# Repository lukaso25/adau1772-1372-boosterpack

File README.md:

# adau1772-1372-boosterpack
4x2 Audio DSP boosterpack primary for EK-TM4C123GXL LaunchPad based on ADAU1772 or ADAU1372 codec.

PCB designed in Eagle 6

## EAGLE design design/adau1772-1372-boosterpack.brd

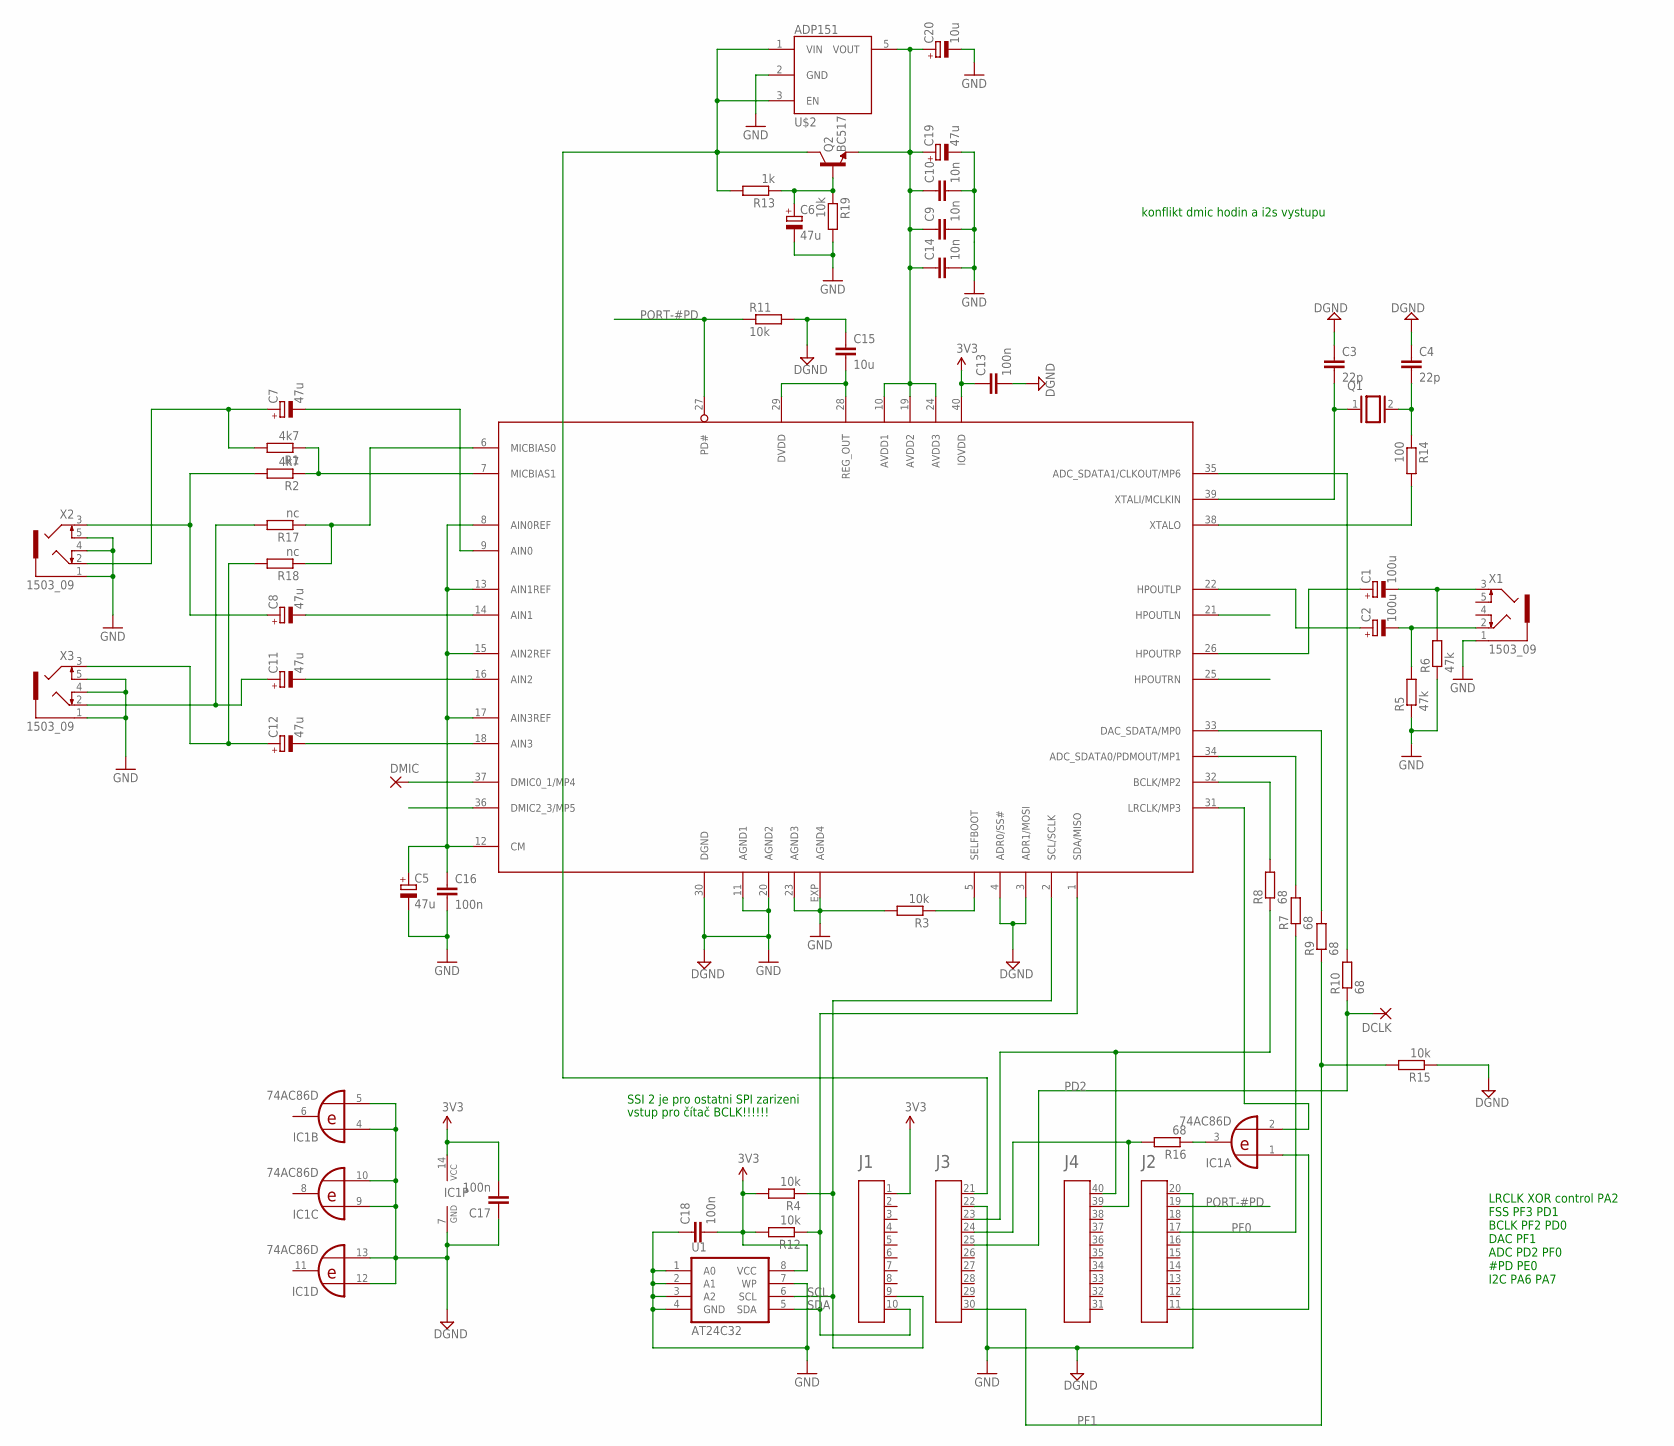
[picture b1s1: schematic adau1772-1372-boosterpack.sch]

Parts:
A1: HEADER4X10-BOOSTERPACK; 4X10-BOOSTERPACK
C1, C2: 100u; E2,5-7
C3, C4: 22p; C0805K
C5: 47u; SMC_C
C6, C7, C8, C11, C12, C19: 47u; E2-5
C9, C10, C14: 10n; C0805
C13, C16, C17, C18: 100n; C0805
C15: 10u; C0805
C20: 10u; SMC_A
DCLK: SMD2; SMD1,27-2,54
DMIC: SMD2; SMD1,27-2,54
IC1: 74AC86D; SO14
Q1: XTAL/S; QS
Q2: BC517; TO92-
R1, R2: 4k7; R1206
R3, R15: 10k; R1206
R4, R11, R12, R19: 10k; R0805
R5, R6: 47k; R0805
R7, R8, R9, R10, R16: 68; R1206
R13: 1k; R0805
R14: 100; R0805
R17, R18: nc; R1206
U1: AT24C32; SO08-8S1
U$1: ADAU1772; LFPSC-40
U$2: ADP151; SOT23-5
X1, X2, X3: 1503_09

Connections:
3.3V: A1.1, C13.1, C17.2, C18.2, IC1.14 (VCC), R4.2, R12.2, U1.8 (VCC), U$1.40 (IOVDD)
GND: A1.20, A1.22, C3.1, C4.1, C5.-, C6.-, C9.2, C10.2, C13.2, C14.2, C15.1, C16.2, C17.1, C18.1, C19.-, C20.-, IC1.4 (I0), IC1.5 (I1), IC1.7 (GND), IC1.9 (I0), IC1.10 (I1), IC1.12 (I0), IC1.13 (I1), R3.2, R5.1, R6.1, R11.2, R15.1, R19.2, U1.1 (A0), U1.2 (A1), U1.3 (A2), U1.4 (GND), U1.7 (WP), U$1.3 (ADR1/MOSI), U$1.4 (ADR0/SS#), U$1.11 (AGND1), U$1.20 (AGND2), U$1.23 (AGND3), U$1.30 (DGND), U$1.EXP (AGND4), U$2.2 (GND), X1.1, X2.1, X2.4, X2.5, X3.1, X3.4, X3.5
unnamed: C8.+, R2.2, X2.3
unnamed: C7.+, R1.2, X2.2
unnamed: C12.-, U$1.18 (AIN3)
unnamed: A1.21, Q2.3 (C), R13.2, U$2.1 (VIN), U$2.3 (EN)
unnamed: C12.+, R18.2, X3.3
unnamed: C11.+, R17.2, X3.2
unnamed: IC1.2 (I1), U$1.31 (LRCLK/MP3)
unnamed: C9.1, C10.1, C14.1, C19.+, C20.+, Q2.1 (E), U$1.10 (AVDD1), U$1.19 (AVDD2), U$1.24 (AVDD3), U$2.5 (VOUT)
unnamed: C1.+, U$1.26 (HPOUTRP)
unnamed: R1.1, R2.1, U$1.7 (MICBIAS1)
unnamed: C2.-, R5.2, X1.2
unnamed: C1.-, R6.2, X1.3
unnamed: R8.2, U$1.32 (BCLK/MP2)
unnamed: C2.+, U$1.22 (HPOUTLP)
unnamed: R7.2, U$1.34 (ADC_SDATA0/PDMOUT/MP1)
unnamed: R10.2, U$1.35 (ADC_SDATA1/CLKOUT/MP6)
unnamed: C3.2, Q1.1, U$1.39 (XTALI/MCLKIN)
unnamed: C4.2, Q1.2, R14.1
unnamed: R14.2, U$1.38 (XTALO)
unnamed: R9.2, U$1.33 (DAC_SDATA/MP0)
unnamed: DMIC.1, U$1.37 (DMIC0_1/MP4)
unnamed: C15.2, U$1.28 (REG_OUT), U$1.29 (DVDD)
unnamed: C11.-, U$1.16 (AIN2)
unnamed: R17.1, R18.1, U$1.6 (MICBIAS0)
unnamed: IC1.3 (O), R16.1
unnamed: A1.11, IC1.1 (I0)
unnamed: A1.24, A1.39, R16.2
unnamed: C6.+, Q2.2 (B), R13.1, R19.1
unnamed: A1.23, A1.40, R8.1
unnamed: R3.1, U$1.5 (SELFBOOT)
unnamed: C7.-, U$1.9 (AIN0)
unnamed: C8.-, U$1.14 (AIN1)
PD2: A1.25, DCLK.1, R10.1
PF0: A1.17, R7.1
PF1: A1.30, R9.1, R15.2
PORT-#PD: A1.19, R11.1, U$1.27 (PD#)
SCL: A1.9, R4.1, U1.6 (SCL), U$1.2 (SCL/SCLK)
SDA: A1.10, R12.1, U1.5 (SDA), U$1.1 (SDA/MISO)
VREF: C5.+, C16.1, U$1.8 (AIN0REF), U$1.12 (CM), U$1.13 (AIN1REF), U$1.15 (AIN2REF), U$1.17 (AIN3REF)

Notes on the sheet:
konflikt dmic hodin a i2s vystupu
SSI 2 je pro ostatni SPI zarizeni
vstup pro čítač BCLK!!!!!!
LRCLK XOR control PA2 FSS PF3 PD1 BCLK PF2 PD0 DAC PF1 ADC PD2 PF0 #PD PE0 I2C PA6 PA7

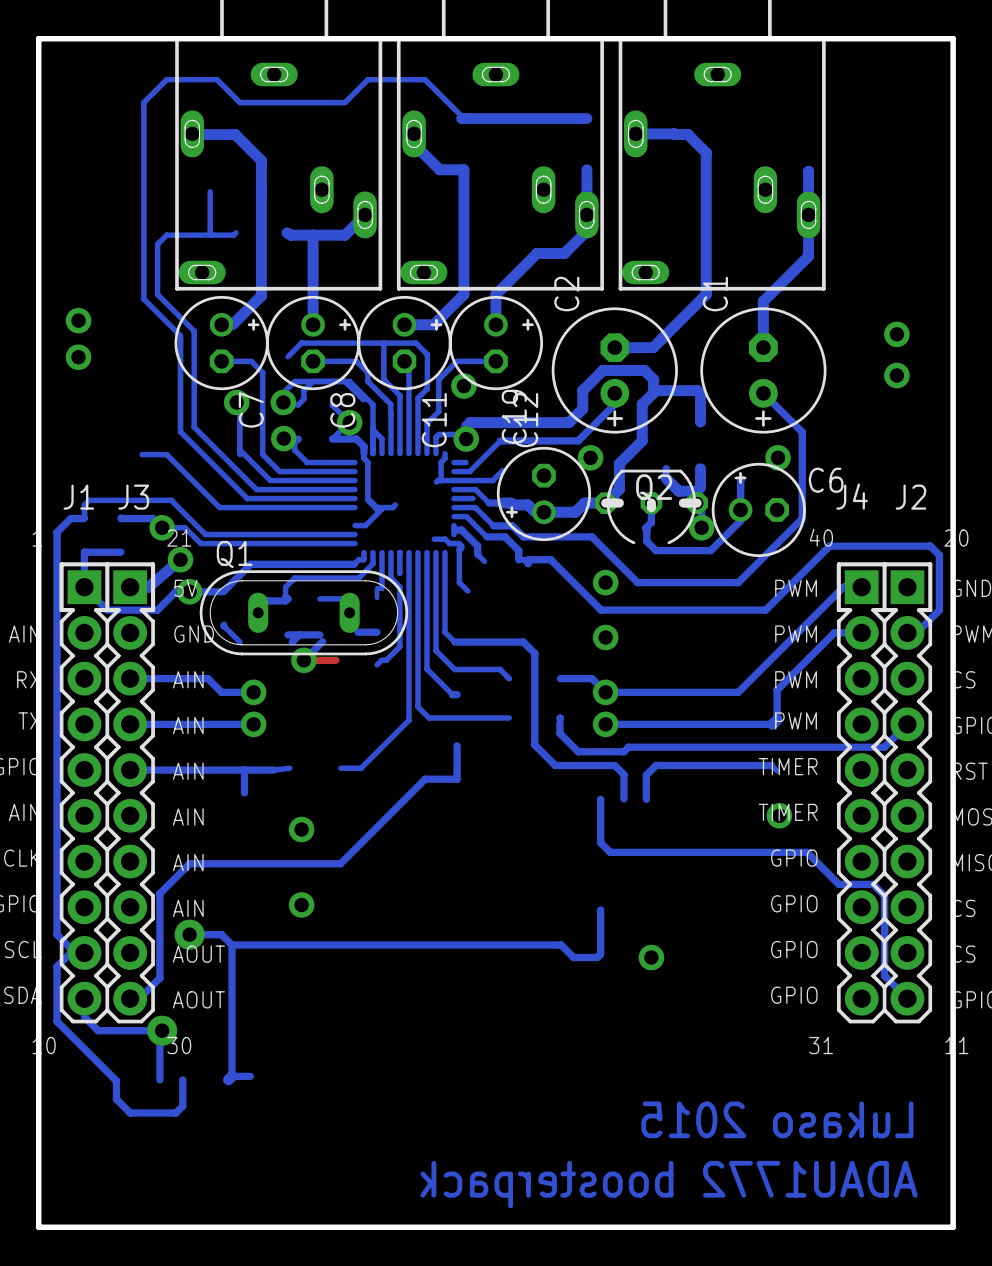
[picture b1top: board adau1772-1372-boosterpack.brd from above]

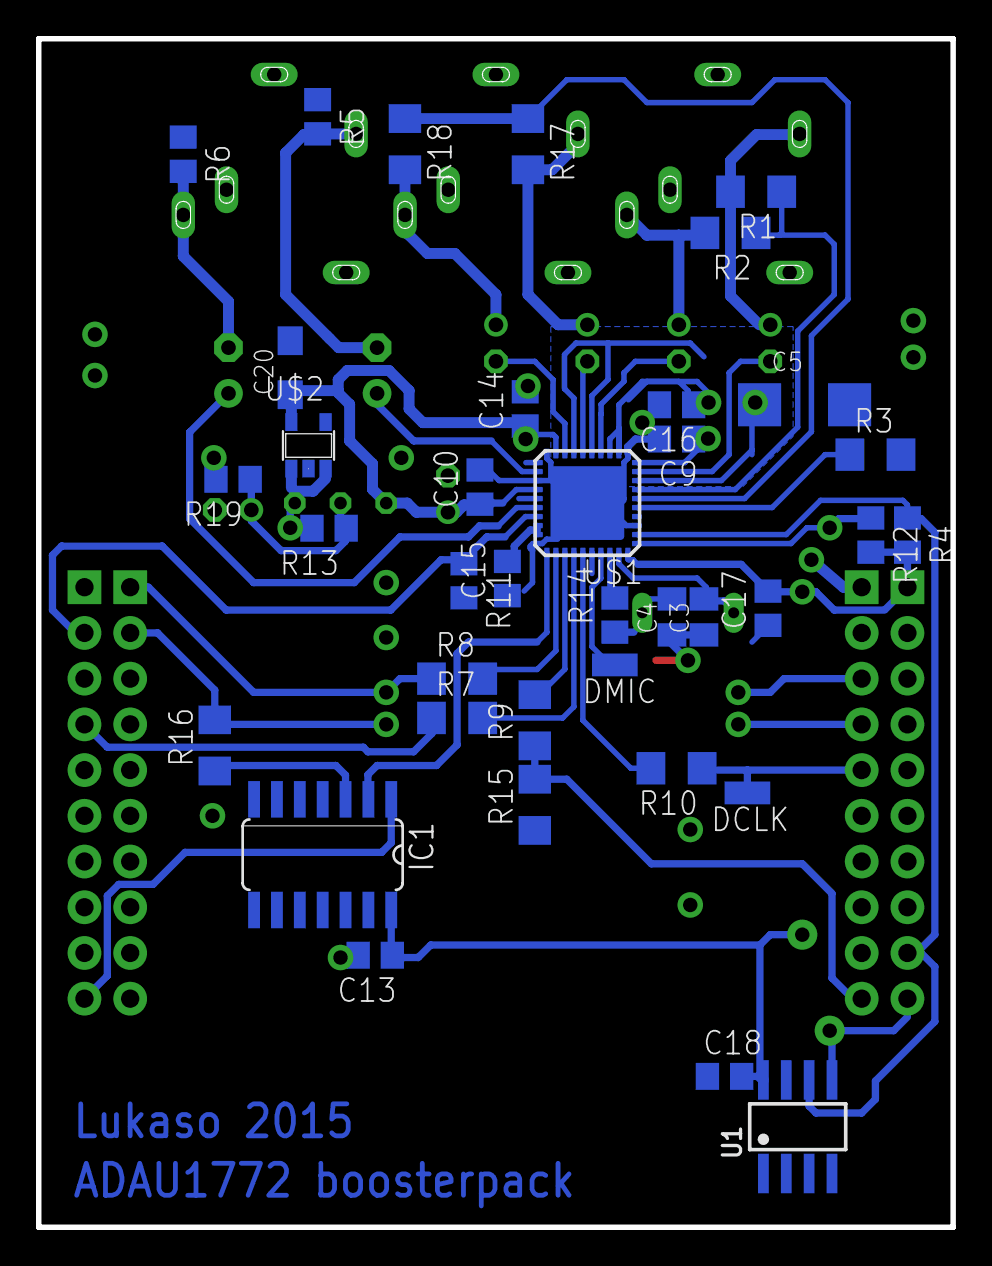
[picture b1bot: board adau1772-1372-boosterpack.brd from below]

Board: 2 copper layers, 50.8 x 66.0 mm, 51 parts (37 on the bottom side), 41 nets.

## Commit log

2016-05-10 First commit, Alpha version of design files

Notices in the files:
parts and their libraries:
memory-atmel: Copyright (C) 2008, Bob Starr
